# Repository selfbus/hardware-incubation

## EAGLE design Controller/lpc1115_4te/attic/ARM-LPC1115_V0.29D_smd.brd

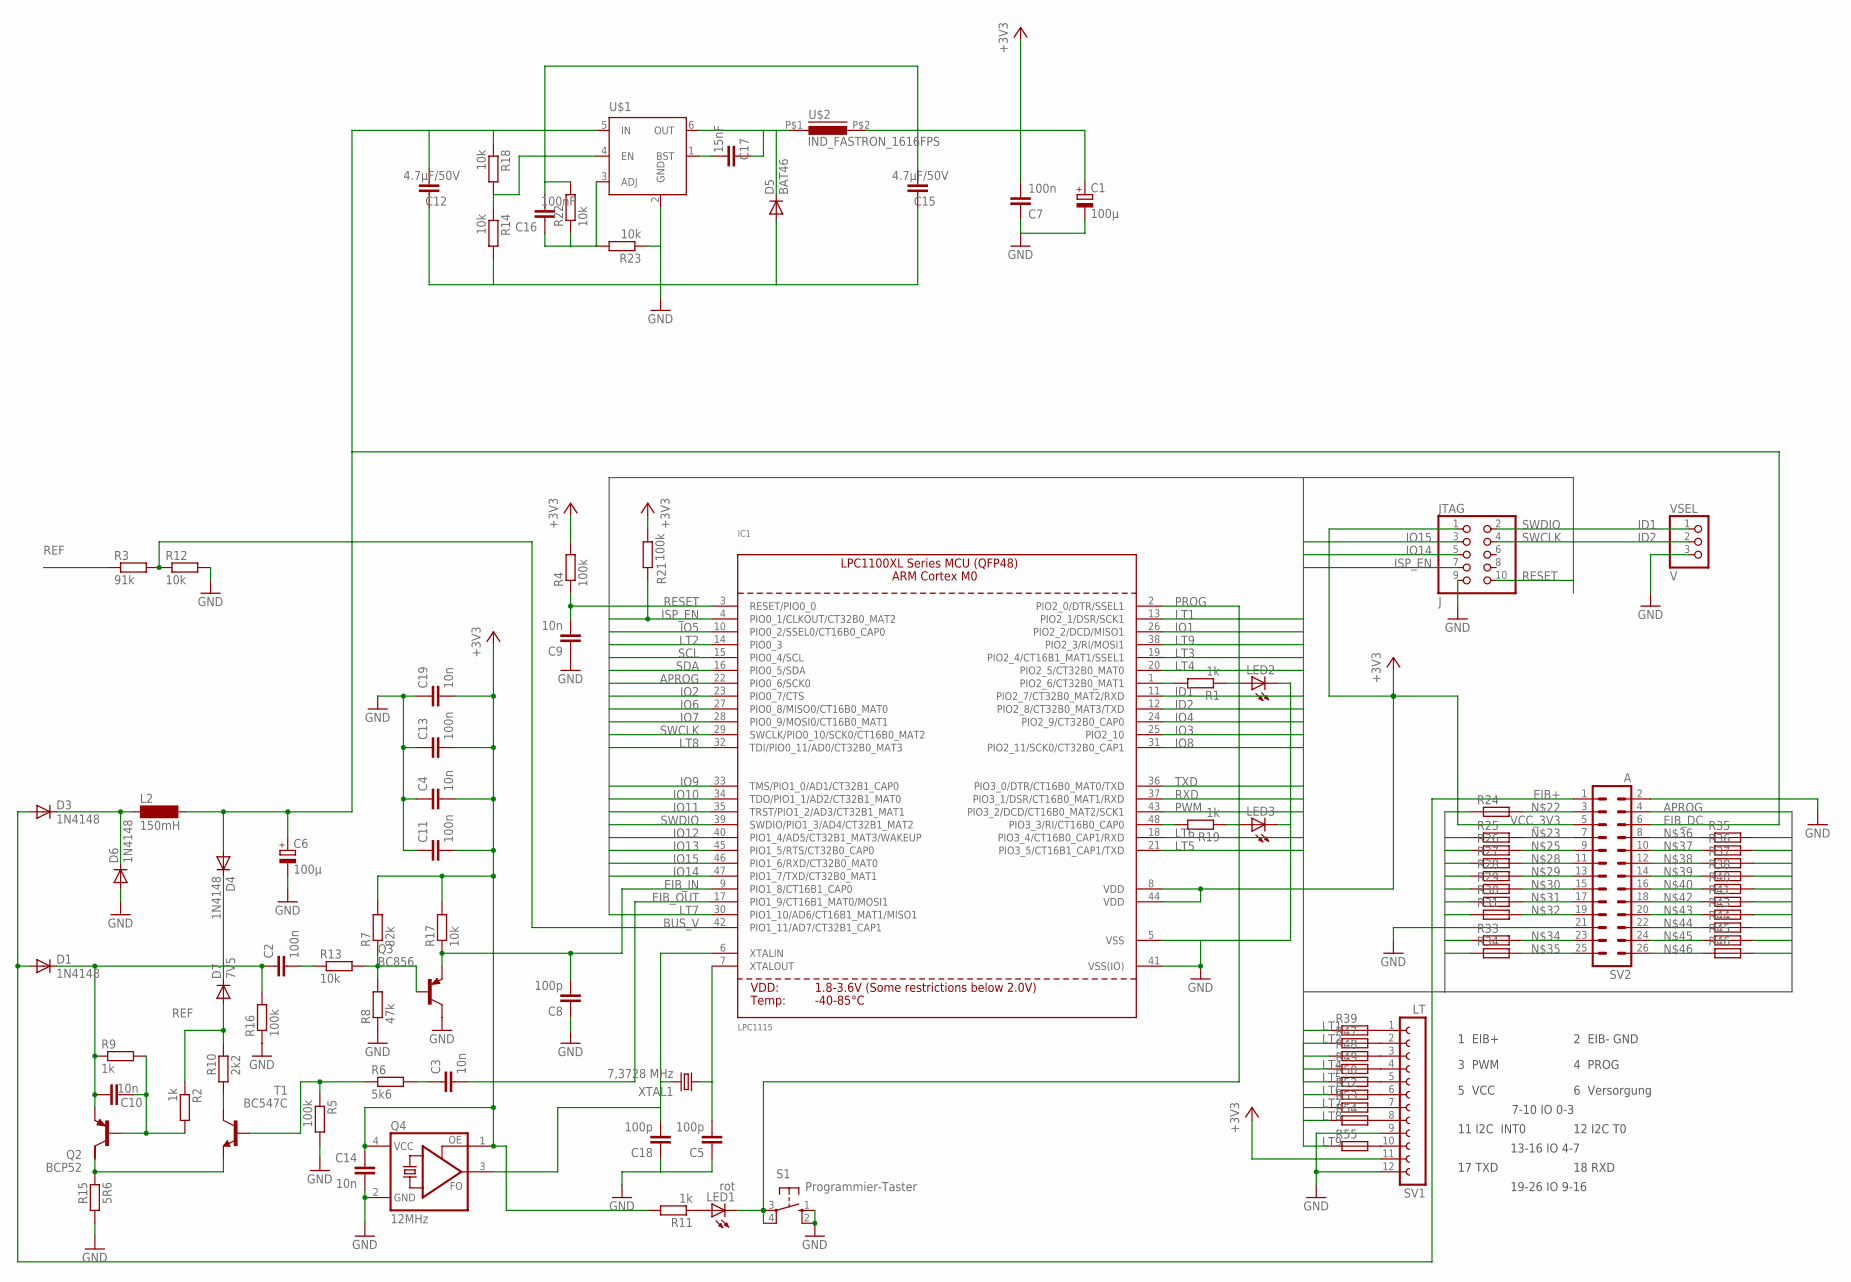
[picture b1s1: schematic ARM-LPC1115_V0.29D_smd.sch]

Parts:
C1, C6: 100µ; E5-8,5
C2: 100n; C1206K
C3, C9, C10: 10n; C1206K
C4, C14, C19: 10n; C1206
C5, C18: 100p; C0603
C7, C11, C13: 100n; C1206
C8: 100p; C1206K
C12, C15: 4.7µF/50V; C1206K
C16: 100nF; C1206
C17: 15nF; C1206
D1, D3, D4, D6: 1N4148; MINIMELF
D5: BAT46; DO214AC
D7: 7V5; MINIMELF
IC1: LPC1115; LQFP48
JTAG: J; 2X05M
L2: 150mH; SD12_1000
LED1: rot; LED3MM
LED2, LED3: LEDSMT1206; 1206
Q2: BCP52; SOT223
Q3: BC856; SOT23-BEC
Q4: 12MHz; ASF
R1, R2, R9, R11, R19: 1k; R1206
R3: 91k; R1206
R4, R5, R16, R21: 100k; R1206
R6: 5k6; R1206
R7: 82k; R1206
R8: 47k; R1206
R10: 2k2; R1206
R12, R13, R14, R17, R18, R22, R23: 10k; R1206
R15: 5R6; R1206
R24, R25, R26, R27, R28, R29, R30, R31, R33, R34, R35, R36, R37, R38, R39, R40, R41, R43, R44, R45, R46, R47, R48, R49, R50, R52, R53, R54, R55: R-EU_BRIDGER0603; R0603_BRIDGE
S1: Programmier-Taster; B3F-10XX
SV1: LT; FE12
SV2: A; ML26
T1: BC547C; SOT23
U$1: BD9G101GBD9G101G-SOT23-6; SOT23-6
U$2: IND_FASTRON_1616FPS; PIS2812
VSEL: V; 1X03_ROUND
XTAL1: 7,3728 MHz; HC49/S

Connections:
APROG: IC1.22 (PIO0_6/SCK0), SV2.4
BUS_V: IC1.42 (PIO1_11/AD7/CT32B1_CAP1), R3.2, R12.1
DRAIN: C2.1, C10.1, D1.C, Q2.3 (E), R9.1, R16.2
EIB+: D1.A, D3.A, SV2.1
EIB_DC: C6.+, C12.2, D4.A, L2.2, R18.1, SV2.6, U$1.5 (IN)
EIB_IN: C8.2, IC1.9 (PIO1_8/CT16B1_CAP0), Q3.E, R17.1
EIB_OUT: C3.2, IC1.17 (PIO1_9/CT16B1_MAT0/MOSI1)
GND: C1.-, C4.1, C5.1, C6.-, C7.1, C8.1, C9.1, C11.1, C12.1, C13.1, C14.2, C15.1, C18.1, C19.1, D5.A, D6.A, IC1.5 (VSS), IC1.41 (VSS(IO)), JTAG.9, LED2.C, LED3.C, Q3.C, Q4.2 (GND), R5.2, R8.1, R12.2, R14.2, R15.1, R16.1, R23.1, S1.1 (S), S1.2 (S1), SV1.9, SV1.12, SV2.2, SV2.21, U$1.2 (GND), VSEL.3
ID1: IC1.11 (PIO2_7/CT32B0_MAT2/RXD), VSEL.1
ID2: IC1.12 (PIO2_8/CT32B0_MAT3/TXD), VSEL.2
IO1: IC1.26 (PIO2_2/DCD/MISO1), R25.1
IO2: IC1.23 (PIO0_7/CTS), R35.2
IO3: IC1.25 (PIO2_10), R26.1
IO4: IC1.24 (PIO2_9/CT32B0_CAP0), R36.2
IO5: IC1.10 (PIO0_2/SSEL0/CT16B0_CAP0), R28.1
IO6: IC1.27 (PIO0_8/MISO0/CT16B0_MAT0), R38.2
IO7: IC1.28 (PIO0_9/MOSI0/CT16B0_MAT1), R29.1
IO8: IC1.31 (PIO2_11/SCK0/CT32B0_CAP1), R40.2
IO9: IC1.33 (TMS/PIO1_0/AD1/CT32B1_CAP0), R31.1
IO10: IC1.34 (TDO/PIO1_1/AD2/CT32B1_MAT0), R43.2
IO11: IC1.35 (TRST/PIO1_2/AD3/CT32B1_MAT1), R44.2
IO12: IC1.40 (PIO1_4/AD5/CT32B1_MAT3/WAKEUP), R33.1
IO13: IC1.45 (PIO1_5/RTS/CT32B0_CAP0), R45.2
IO14: IC1.47 (PIO1_7/TXD/CT32B0_MAT1), JTAG.5, R34.1
IO15: IC1.46 (PIO1_6/RXD/CT32B0_MAT0), JTAG.3, R46.2
ISP_EN: IC1.4 (PIO0_1/CLKOUT/CT32B0_MAT2), JTAG.7, R21.1
LT1: IC1.13 (PIO2_1/DSR/SCK1), R39.1
LT2: IC1.14 (PIO0_3), R47.1
LT3: IC1.19 (PIO2_4/CT16B1_MAT1/SSEL1), R48.1
LT4: IC1.20 (PIO2_5/CT32B0_MAT0), R49.1
LT5: IC1.21 (PIO3_5/CT16B1_CAP1/TXD), R50.1
LT6: IC1.18 (PIO3_4/CT16B0_CAP1/RXD), R52.1
LT7: IC1.30 (PIO1_10/AD6/CT16B1_MAT1/MISO1), R53.1
LT8: IC1.32 (TDI/PIO0_11/AD0/CT32B0_MAT3), R54.1
LT9: IC1.38 (PIO2_3/RI/MOSI1), R55.1
LX: C17.1, D5.C, U$1.6 (OUT), U$2.P$1 (1)
unnamed: C3.1, R6.2
unnamed: C2.2, R13.1
unnamed: C5.2, IC1.7 (XTALOUT), XTAL1.1
unnamed: IC1.1 (PIO2_6/CT32B0_MAT1), R1.2
unnamed: IC1.48 (PIO3_3/RI/CT16B0_CAP0), R19.2
unnamed: R10.1, T1.3 (C)
unnamed: Q2.2 (C), R15.2, T1.2 (E)
unnamed: D3.C, D6.C, L2.1
unnamed: D4.C, D7.C
unnamed: LED2.A, R1.1
unnamed: LED3.A, R19.1
unnamed: R5.1, R6.1, T1.1 (B)
unnamed: Q3.B, R7.1, R8.2, R13.2
unnamed: C10.2, Q2.1 (B), R2.2, R9.2
unnamed: C18.2, IC1.6 (XTALIN), Q4.3 (FO), XTAL1.2
unnamed: C17.2, U$1.1 (BST)
unnamed: R14.1, R18.2, U$1.4 (EN)
unnamed: R24.2, SV2.3
unnamed: R25.2, SV2.7
unnamed: C16.1, R22.1, R23.2, U$1.3 (ADJ)
unnamed: R26.2, SV2.9
unnamed: R27.2, SV2.11
unnamed: R28.2, SV2.13
unnamed: R29.2, SV2.15
unnamed: R30.2, SV2.17
unnamed: R31.2, SV2.19
unnamed: R33.2, SV2.23
unnamed: R34.2, SV2.25
unnamed: R35.1, SV2.8
unnamed: R36.1, SV2.10
unnamed: R37.1, SV2.12
unnamed: R38.1, SV2.14
unnamed: R40.1, SV2.16
unnamed: LED1.A, R11.1
unnamed: R41.1, SV2.18
unnamed: R43.1, SV2.20
unnamed: R44.1, SV2.22
unnamed: R45.1, SV2.24
unnamed: R46.1, SV2.26
unnamed: R39.2, SV1.1
unnamed: R47.2, SV1.2
unnamed: R48.2, SV1.3
unnamed: R49.2, SV1.4
unnamed: R50.2, SV1.5
unnamed: R52.2, SV1.6
unnamed: R53.2, SV1.7
unnamed: R54.2, SV1.8
unnamed: R55.2, SV1.10
PROG: IC1.2 (PIO2_0/DTR/SSEL1), LED1.K (C), S1.3, S1.4 (P1)
PWM: IC1.43 (PIO3_2/DCD/CT16B0_MAT2/SCK1), R24.1
REF: D7.A, R2.1, R3.1, R10.2
RESET: C9.2, IC1.3 (RESET/PIO0_0), JTAG.10, R4.1
RXD: IC1.37 (PIO3_1/DSR/CT16B0_MAT1/RXD), R41.2
SCL: IC1.15 (PIO0_4/SCL), R37.2
SDA: IC1.16 (PIO0_5/SDA), R27.1
SWCLK: IC1.29 (SWCLK/PIO0_10/SCK0/CT16B0_MAT2), JTAG.4
SWDIO: IC1.39 (SWDIO/PIO1_3/AD4/CT32B1_MAT2), JTAG.2
TXD: IC1.36 (PIO3_0/DTR/CT16B0_MAT0/TXD), R30.1
VCC_3V3: C1.+, C4.2, C7.2, C11.2, C13.2, C14.1, C15.2, C16.2, C19.2, IC1.8 (VDD), IC1.44 (VDD), JTAG.1, Q4.1 (OE), Q4.4 (VCC), R4.2, R7.2, R11.2, R17.2, R21.2, R22.2, SV1.11, SV2.5, U$2.P$2 (2)

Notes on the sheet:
1 EIB+
2 EIB- GND
3 PWM
4 PROG
5 VCC
6 Versorgung
7-10 IO 0-3
11 I2C INT0
12 I2C T0
13-16 IO 4-7
17 TXD
18 RXD
19-26 IO 9-16

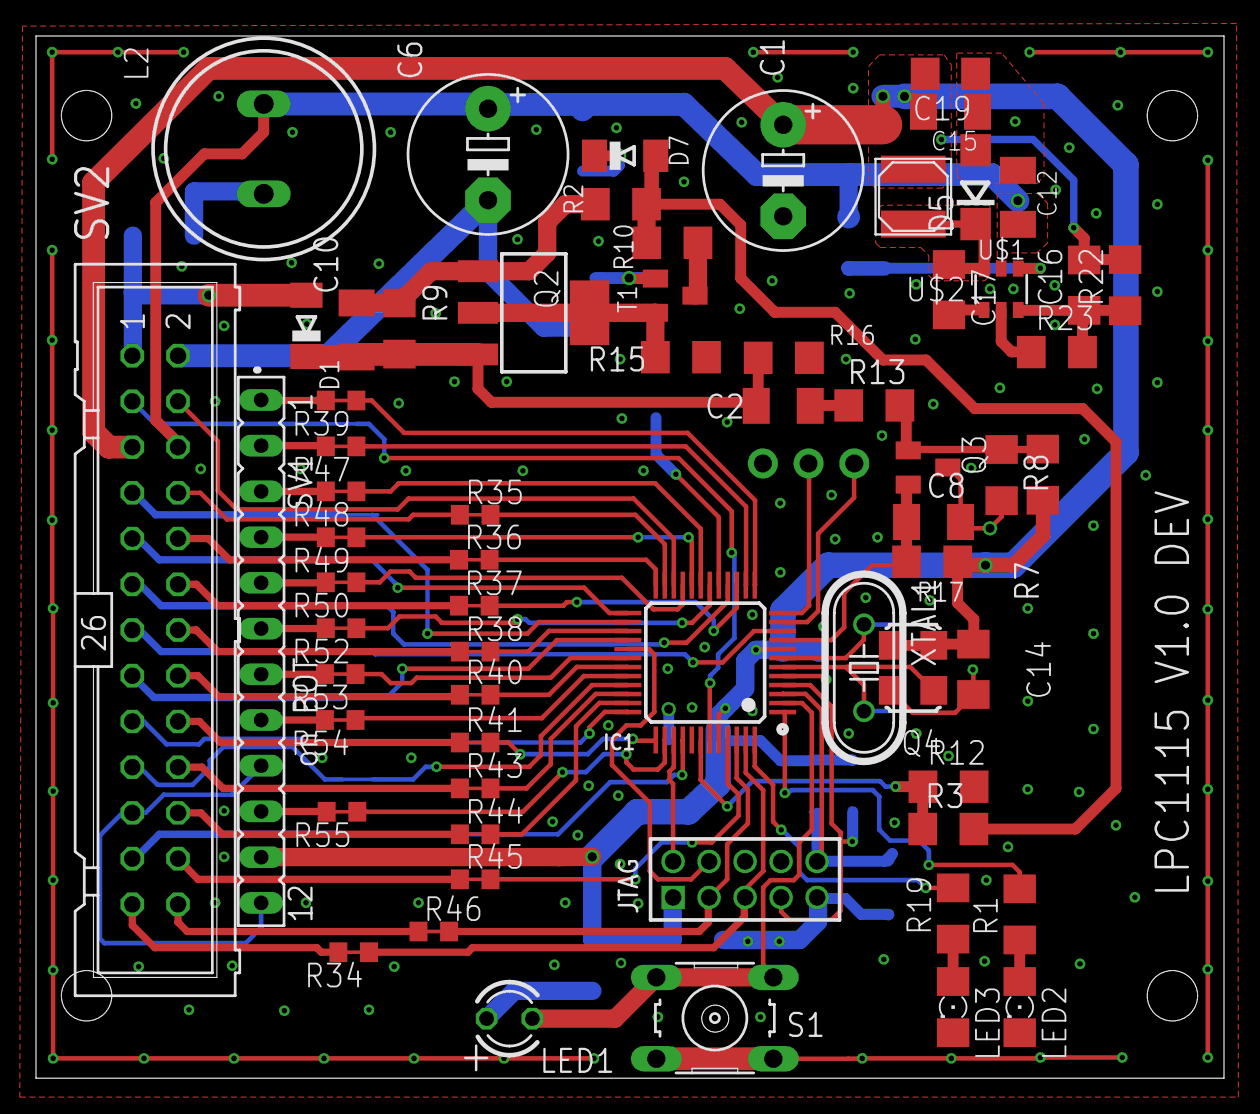
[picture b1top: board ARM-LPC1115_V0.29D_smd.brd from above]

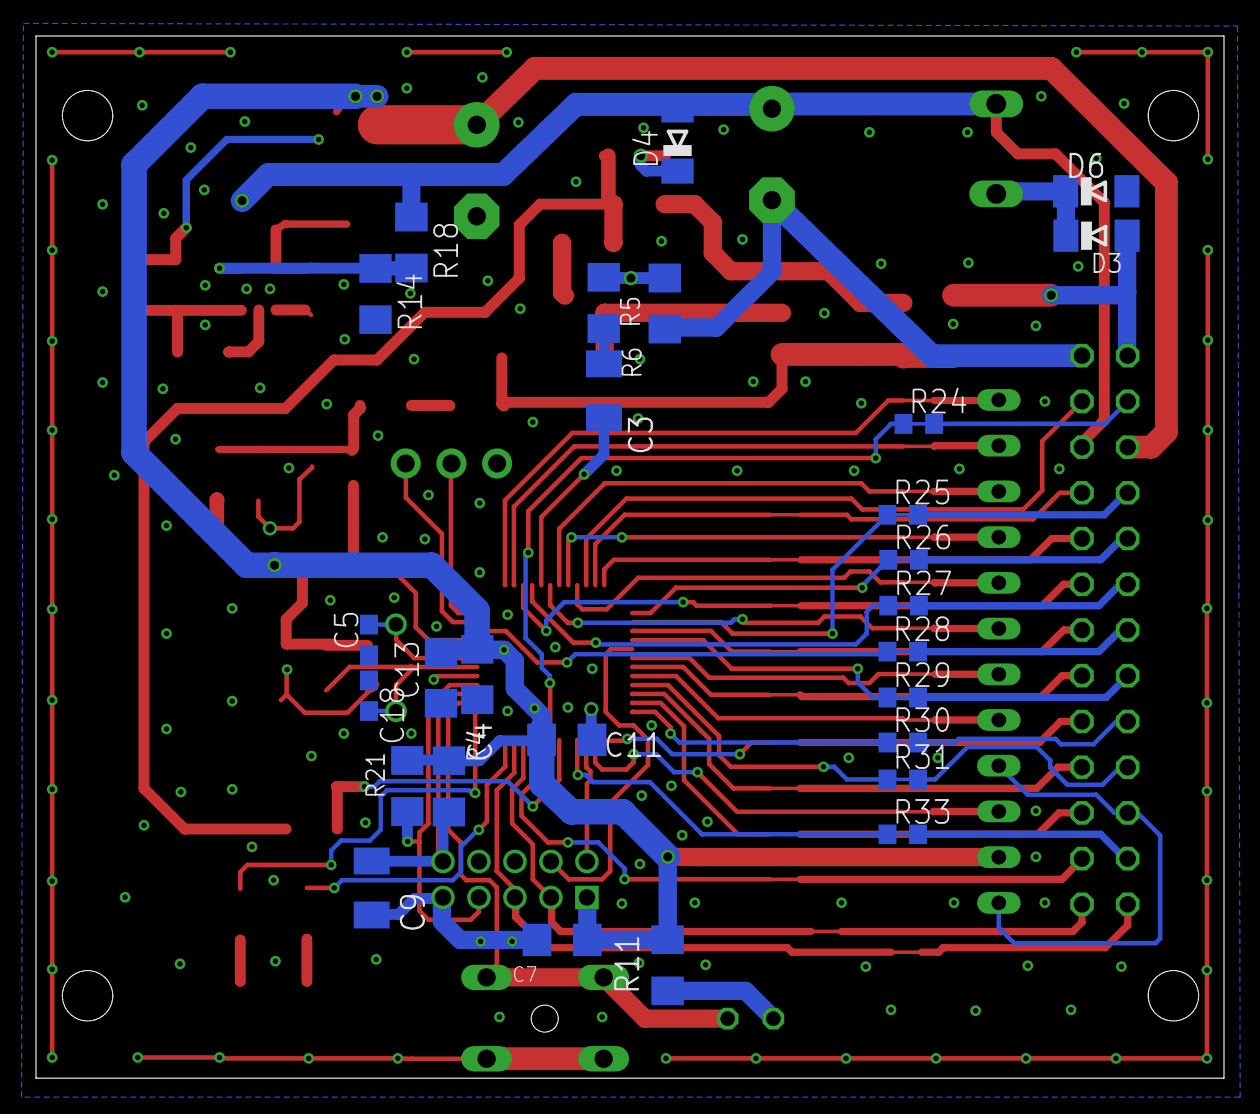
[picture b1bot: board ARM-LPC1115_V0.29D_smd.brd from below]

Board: 2 copper layers, 66.0 x 57.9 mm, 93 parts (27 on the bottom side), 95 nets.

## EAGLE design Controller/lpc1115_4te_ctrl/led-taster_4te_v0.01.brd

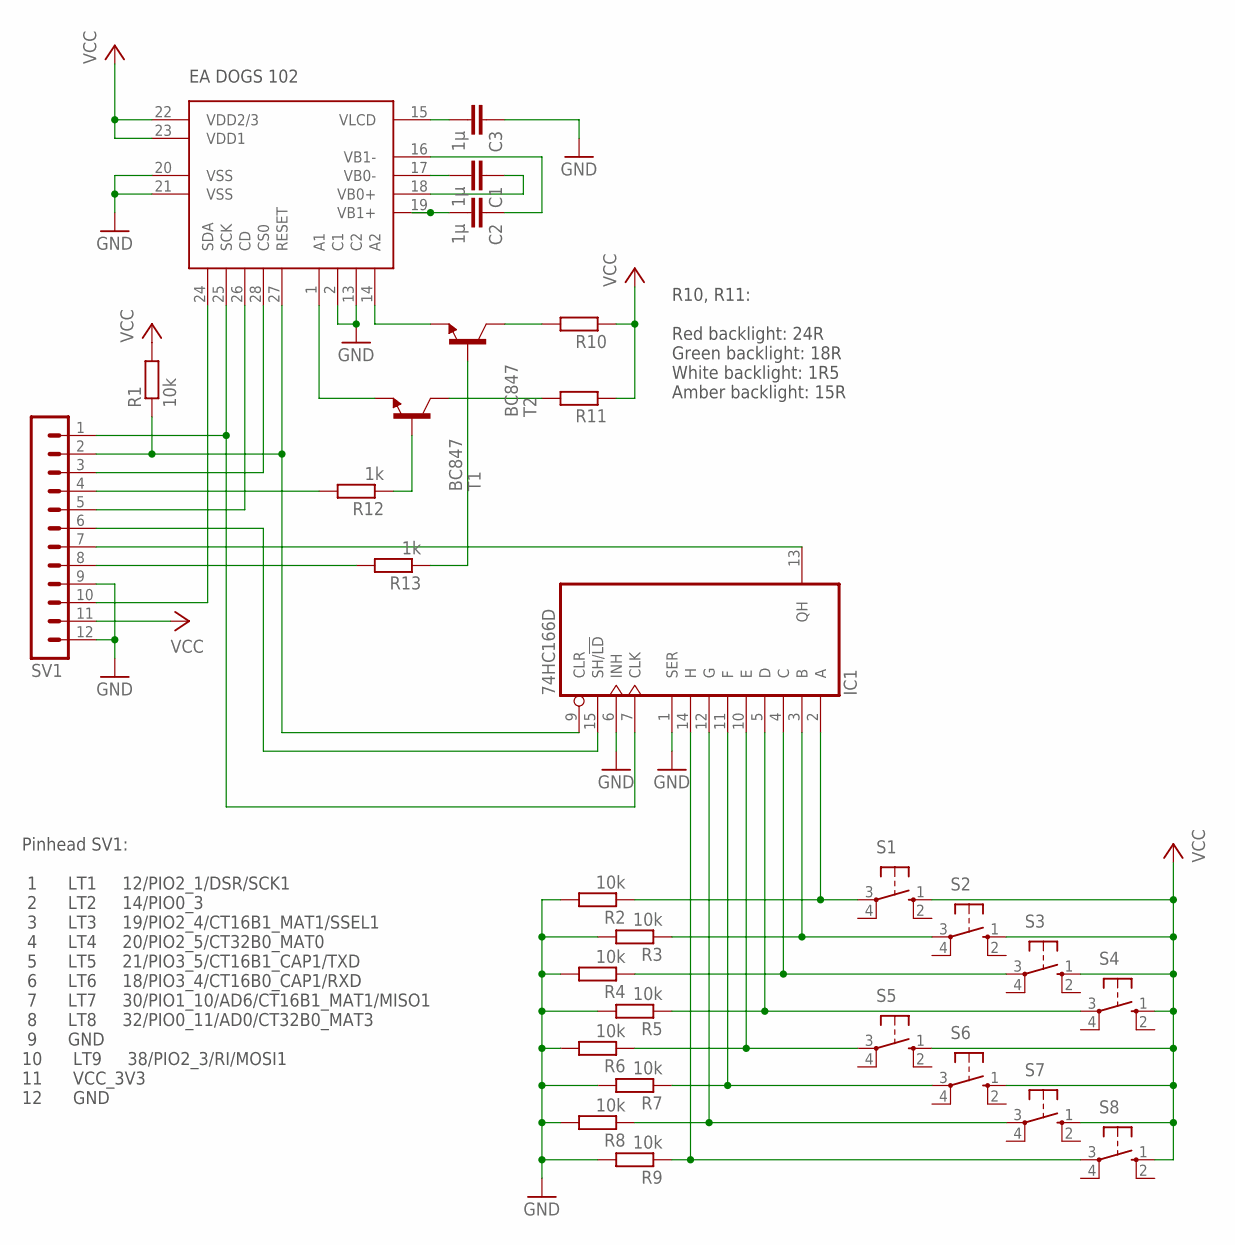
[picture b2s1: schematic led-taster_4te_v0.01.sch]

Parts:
C1, C2, C3: 1µ; C1210
EA_DOGS102: DOGS102
IC1: 74HC166D; SO16
R1, R2, R3, R4, R5, R6, R7, R8, R9: 10k; R1206
R10, R11: R-EU_R1206; R1206
R12, R13: 1k; R1206
S1, S2, S3, S4, S5, S6, S7, S8: 10-XX; B3F-10XX
SV1: MA12-1
T1, T2: BC847; SOT23

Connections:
+3V3: EA_DOGS102.22 (VDD2/3), EA_DOGS102.23 (VDD1), IC1.16 (VCC), R1.2, R10.1, R11.1, S1.1 (S), S2.1 (S), S3.1 (S), S4.1 (S), S5.1 (S), S6.1 (S), S7.1 (S), S8.1 (S), SV1.11
GND: C3.1, EA_DOGS102.2 (C1), EA_DOGS102.13 (C2), EA_DOGS102.20 (VSS), EA_DOGS102.21 (VSS), IC1.1 (SER), IC1.6 (INH), IC1.8 (GND), R2.2, R3.2, R4.2, R5.2, R6.2, R7.2, R8.2, R9.2, SV1.9, SV1.12
MISO: IC1.13 (QH), SV1.7
MOSI: EA_DOGS102.24 (SDA), SV1.10
unnamed: IC1.2 (A), R2.1, S1.3
unnamed: C2.2, EA_DOGS102.19 (VB1+)
unnamed: C2.1, EA_DOGS102.16 (VB1-)
unnamed: C1.2, EA_DOGS102.17 (VB0-)
unnamed: C1.1, EA_DOGS102.18 (VB0+)
unnamed: C3.2, EA_DOGS102.15 (VLCD)
unnamed: IC1.3 (B), R3.1, S2.3
unnamed: IC1.4 (C), R4.1, S3.3
unnamed: IC1.5 (D), R5.1, S4.3
unnamed: IC1.10 (E), R6.1, S5.3
unnamed: IC1.14 (H), R9.1, S8.3
unnamed: IC1.12 (G), R8.1, S7.3
unnamed: IC1.11 (F), R7.1, S6.3
unnamed: EA_DOGS102.28 (CS0), SV1.3
unnamed: EA_DOGS102.1 (A1), T1.2 (E)
unnamed: EA_DOGS102.14 (A2), T2.2 (E)
unnamed: R10.2, T2.3 (C)
unnamed: R11.2, T1.3 (C)
unnamed: R13.1, T2.1 (B)
unnamed: R12.1, T1.1 (B)
unnamed: R12.2, SV1.4
unnamed: R13.2, SV1.8
unnamed: IC1.15 (SH/!LD), SV1.6
unnamed: EA_DOGS102.26 (CD), SV1.5
RESET: EA_DOGS102.27 (RESET), IC1.9 (CLR), R1.1, SV1.2
SCK: EA_DOGS102.25 (SCK), IC1.7 (CLK), SV1.1

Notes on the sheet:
Pinhead SV1: 1 LT1 12/PIO2_1/DSR/SCK1 2 LT2 14/PIO0_3 3 LT3 19/PIO2_4/CT16B1_MAT1/SSEL1 4 LT4 20/PIO2_5/CT32B0_MAT0 5 LT5 21/PIO3_5/CT16B1_CAP1/TXD 6 LT6 18/PIO3_4/CT16B0_CAP1/RXD 7 LT7 30/PIO1_10/AD6/CT16B1_MAT1/MISO1 8 LT8 32/PIO0_11/AD0/CT32B0_MAT3 9 GND 10 LT9 38/PIO2_3/RI/MOSI1 11 VCC_3V3 12 G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
R10, R11: Red backlight: 24R Green backlight: 18R White backlight: 1R5 Amber backlight: 15R
EA DOGS 102

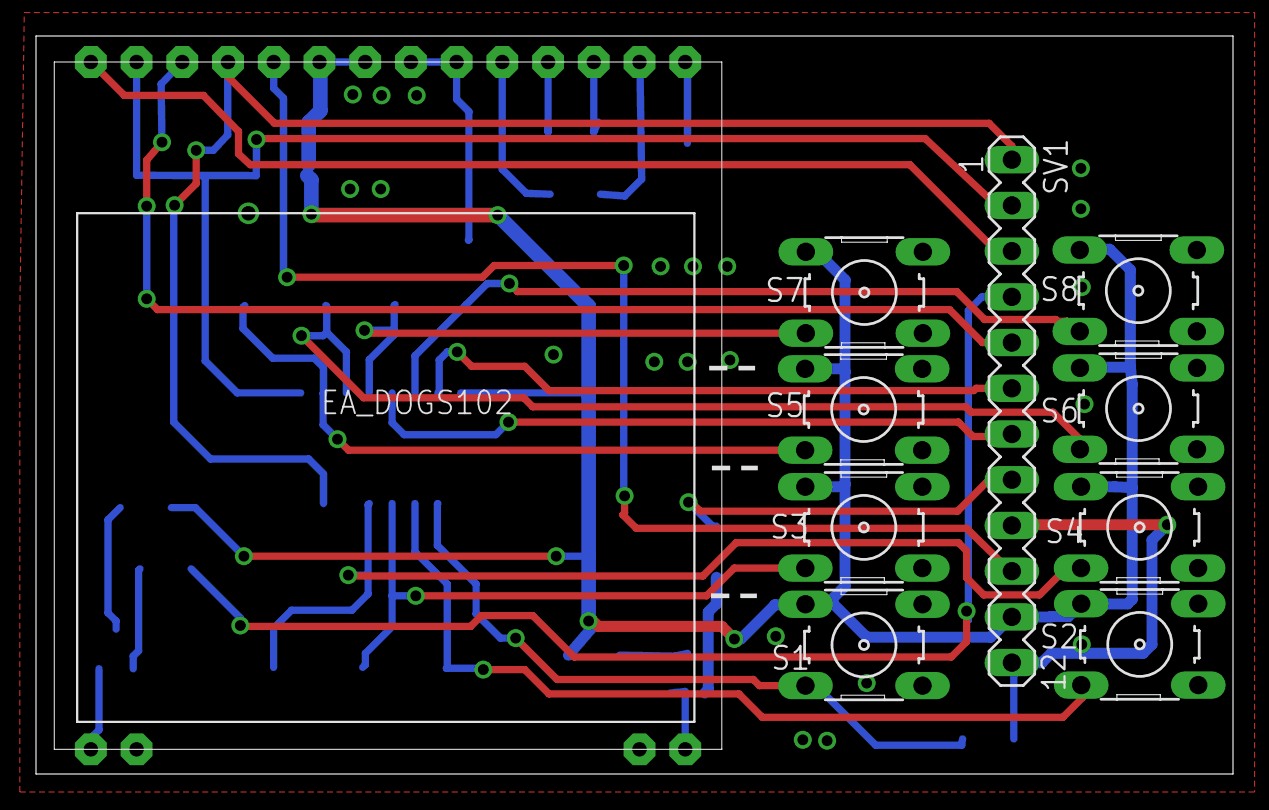
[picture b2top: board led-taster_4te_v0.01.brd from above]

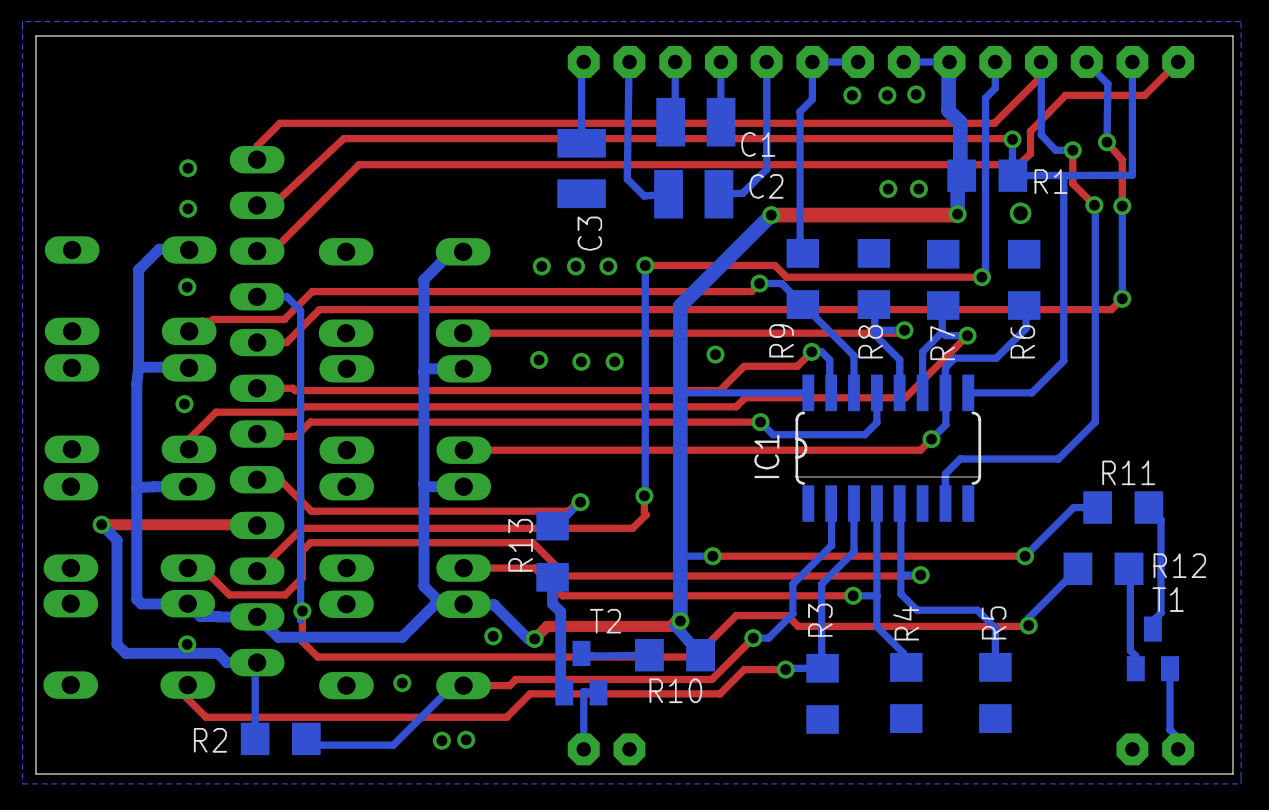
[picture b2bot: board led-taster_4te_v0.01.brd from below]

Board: 2 copper layers, 66.5 x 41.0 mm, 29 parts (19 on the bottom side), 30 nets.

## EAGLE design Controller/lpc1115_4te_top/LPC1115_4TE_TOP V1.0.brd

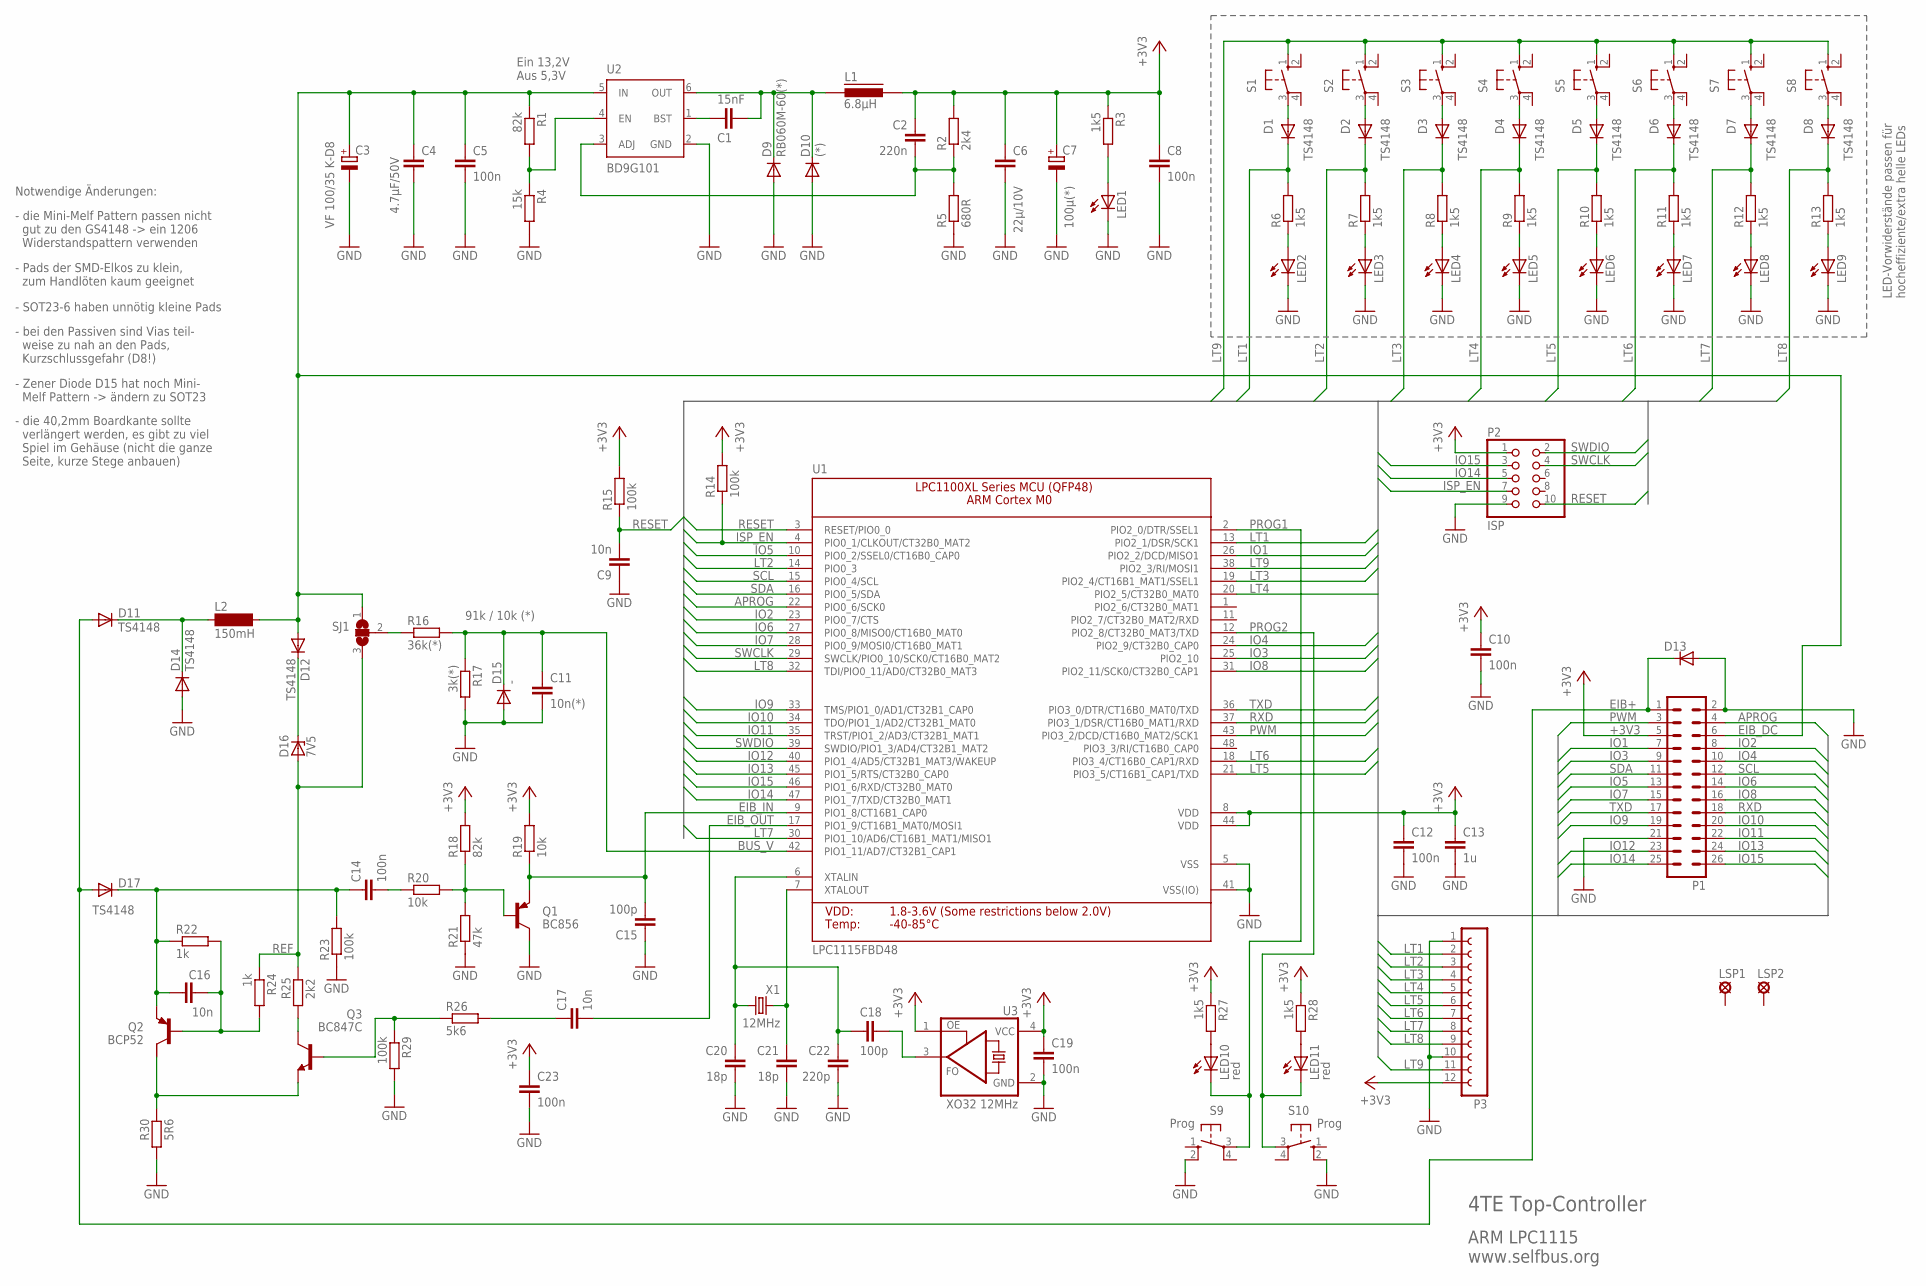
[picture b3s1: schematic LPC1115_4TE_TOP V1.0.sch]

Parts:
C1: 15nF; R0805M
C2: 220n; R0805M
C3: VF 100/35 K-D8; UD-6,3X7,7_NICHICON
C4: 4.7µF/50V; R1206M
C5, C8, C10, C12, C14, C19, C23: 100n; R0805M
C6: 22µ/10V; C1210K
C7: 100µ(*); UD-6,3X7,7_NICHICON
C9, C16, C17: 10n; R0805M
C11: 10n(*); R0805M
C13: 1u; R0805M
C15, C18: 100p; R0805M
C20, C21: 18p; R0805M
C22: 220p; R0805M
D1, D2, D3, D4, D5, D6, D7, D8, D11, D12, D14, D17: TS4148; MINIMELF
D9: RB060M-60(*); SOD123
D10: (*); SMB
D13: D-SMB; SMB
D15: -; MINIMELF
D16: 7V5; SOT23
L1: 6.8µH; 1616FPS
L2: 150mH; BS11_LIEGEND
LED1, LED2, LED3, LED4, LED5, LED6, LED7, LED8, LED9: LEDSMT1206; 1206
LED10, LED11: red; 1206
LSP1, LSP2: SE13_SM
P1: ML26
P2: ISP; 2X05M
P3: FE12-1; FE12
Q1: BC856; SOT23-BEC
Q2: BCP52; SOT223
Q3: BC847C; SOT23
R1, R18: 82k; R0805M
R2: 2k4; R0805M
R3, R6, R7, R8, R9, R10, R11, R12, R13, R27, R28: 1k5; R0805M
R4: 15k; R0805M
R5: 680R; R0805M
R14, R15, R23, R29: 100k; R0805M
R16: 36k(*); R0805M
R17: 3k(*); R0805M
R19, R20: 10k; R0805M
R21: 47k; R0805M
R22, R24: 1k; R0805M
R25: 2k2; R0805M
R26: 5k6; R0805M
R30: 5R6; R1206M
S1, S2, S3, S4, S5, S6, S7, S8: 10-XXSMD; B3F-10XX_SMD
S9, S10: Prog; B3F-10XX_SMD
SJ1: SJ2W; SJ_2
U1: LPC1115FBD48; LQFP48
U2: BD9G101; SOT23-6
U3: XO32 12MHz; ASF
X1: 12MHz; ASF

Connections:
+3V3: C2.1, C6.1, C7.+, C8.1, C10.1, C12.1, C13.1, C19.1, C23.1, L1.P$2 (2), P1.5, P2.1, P3.12, R2.2, R3.1, R14.2, R15.2, R18.2, R19.2, R27.1, R28.1, U1.8 (VDD), U1.44 (VDD), U3.1 (OE), U3.4 (VCC)
APROG: P1.4, U1.22 (PIO0_6/SCK0)
BUS_V: C11.1, D15.C, R16.2, R17.1, U1.42 (PIO1_11/AD7/CT32B1_CAP1)
DRAIN: C14.1, C16.1, D17.C, Q2.3 (E), R22.1, R23.2
EIB+: D11.A, D13.1 (C), D17.A, P1.1
EIB_DC: C3.+, C4.1, C5.1, D12.A, L2.2, P1.6, R1.1, SJ1.1, U2.5 (IN)
EIB_IN: C15.2, Q1.E, R19.1, U1.9 (PIO1_8/CT16B1_CAP0)
EIB_OUT: C17.2, U1.17 (PIO1_9/CT16B1_MAT0/MOSI1)
GND: C3.-, C4.2, C5.2, C6.2, C7.-, C8.2, C9.1, C10.2, C11.2, C12.2, C13.2, C15.1, C19.2, C20.2, C21.2, C22.2, C23.2, D9.A, D10.A, D13.2 (A), D14.A, D15.A, LED1.C, LED2.C, LED3.C, LED4.C, LED5.C, LED6.C, LED7.C, LED8.C, LED9.C, P1.2, P1.21, P2.9, P3.1, P3.10, Q1.C, R4.2, R5.1, R17.2, R21.1, R23.1, R29.2, R30.1, S9.2 (S1), S10.2 (S1), U1.5 (VSS), U1.41 (VSS(IO)), U2.2 (GND), U3.2 (GND)
IO1: P1.7, U1.26 (PIO2_2/DCD/MISO1)
IO2: P1.8, U1.23 (PIO0_7/CTS)
IO3: P1.9, U1.25 (PIO2_10)
IO4: P1.10, U1.24 (PIO2_9/CT32B0_CAP0)
IO5: P1.13, U1.10 (PIO0_2/SSEL0/CT16B0_CAP0)
IO6: P1.14, U1.27 (PIO0_8/MISO0/CT16B0_MAT0)
IO7: P1.15, U1.28 (PIO0_9/MOSI0/CT16B0_MAT1)
IO8: P1.16, U1.31 (PIO2_11/SCK0/CT32B0_CAP1)
IO9: P1.19, U1.33 (TMS/PIO1_0/AD1/CT32B1_CAP0)
IO10: P1.20, U1.34 (TDO/PIO1_1/AD2/CT32B1_MAT0)
IO11: P1.22, U1.35 (TRST/PIO1_2/AD3/CT32B1_MAT1)
IO12: P1.23, U1.40 (PIO1_4/AD5/CT32B1_MAT3/WAKEUP)
IO13: P1.24, U1.45 (PIO1_5/RTS/CT32B0_CAP0)
IO14: P1.25, P2.5, U1.47 (PIO1_7/TXD/CT32B0_MAT1)
IO15: P1.26, P2.3, U1.46 (PIO1_6/RXD/CT32B0_MAT0)
ISP_EN: P2.7, R14.1, U1.4 (PIO0_1/CLKOUT/CT32B0_MAT2)
LT1: D1.C, P3.2, R6.2, U1.13 (PIO2_1/DSR/SCK1)
LT2: D2.C, P3.3, R7.2, U1.14 (PIO0_3)
LT3: D3.C, P3.4, R8.2, U1.19 (PIO2_4/CT16B1_MAT1/SSEL1)
LT4: D4.C, P3.5, R9.2, U1.20 (PIO2_5/CT32B0_MAT0)
LT5: D5.C, P3.6, R10.2, U1.21 (PIO3_5/CT16B1_CAP1/TXD)
LT6: D6.C, P3.7, R11.2, U1.18 (PIO3_4/CT16B0_CAP1/RXD)
LT7: D7.C, P3.8, R12.2, U1.30 (PIO1_10/AD6/CT16B1_MAT1/MISO1)
LT8: D8.C, P3.9, R13.2, U1.32 (TDI/PIO0_11/AD0/CT32B0_MAT3)
LT9: P3.11, S1.1 (S), S2.1 (S), S3.1 (S), S4.1 (S), S5.1 (S), S6.1 (S), S7.1 (S), S8.1 (S), U1.38 (PIO2_3/RI/MOSI1)
LX: C1.1, D9.C, D10.C, L1.P$1 (1), U2.6 (OUT)
unnamed: C17.1, R26.2
unnamed: C14.2, R20.1
unnamed: C21.1, U1.7 (XTALOUT), X1.1
unnamed: LED11.A, R28.2
unnamed: R16.1, SJ1.2
unnamed: Q3.3 (C), R25.1
unnamed: Q2.2 (C), Q3.2 (E), R30.2
unnamed: D11.C, D14.C, L2.1
unnamed: D12.C, D16.3 (C)
unnamed: Q3.1 (B), R26.1, R29.1
unnamed: LED1.A, R3.2
unnamed: Q1.B, R18.1, R20.2, R21.2
unnamed: C16.2, Q2.1 (B), R22.2, R24.2
unnamed: C18.1, U3.3 (FO)
unnamed: D8.A, S8.3
unnamed: C1.2, U2.1 (BST)
unnamed: R1.2, R4.1, U2.4 (EN)
unnamed: C18.2, C20.1, C22.1, U1.6 (XTALIN), X1.3 (2)
unnamed: D7.A, S7.3
unnamed: C2.2, R2.1, R5.2, U2.3 (ADJ)
unnamed: LED2.A, R6.1
unnamed: D6.A, S6.3
unnamed: D5.A, S5.3
unnamed: D4.A, S4.3
unnamed: D3.A, S3.3
unnamed: D2.A, S2.3
unnamed: LED3.A, R7.1
unnamed: D1.A, S1.3
unnamed: LED10.A, R27.2
unnamed: LED4.A, R8.1
unnamed: LED5.A, R9.1
unnamed: LED6.A, R10.1
unnamed: LED7.A, R11.1
unnamed: LED8.A, R12.1
unnamed: LED9.A, R13.1
PROG1: LED10.C, S9.3, U1.2 (PIO2_0/DTR/SSEL1)
PROG2: LED11.C, S10.3, U1.12 (PIO2_8/CT32B0_MAT3/TXD)
PWM: P1.3, U1.43 (PIO3_2/DCD/CT16B0_MAT2/SCK1)
REF: D16.1 (A), R24.1, R25.2, SJ1.3
RESET: C9.2, P2.10, R15.1, U1.3 (RESET/PIO0_0)
RXD: P1.18, U1.37 (PIO3_1/DSR/CT16B0_MAT1/RXD)
SCL: P1.12, U1.15 (PIO0_4/SCL)
SDA: P1.11, U1.16 (PIO0_5/SDA)
SWCLK: P2.4, U1.29 (SWCLK/PIO0_10/SCK0/CT16B0_MAT2)
SWDIO: P2.2, U1.39 (SWDIO/PIO1_3/AD4/CT32B1_MAT2)
TXD: P1.17, U1.36 (PIO3_0/DTR/CT16B0_MAT0/TXD)

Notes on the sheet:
4TE Top-Controller
ARM LPC1115 www.selfbus.org
Ein 13,2V Aus 5,3V
- die Mini-Melf Pattern passen nicht gut zu den GS4148 -> ein 1206 Widerstandspattern verwenden
Notwendige Änderungen:
91k / 10k (*)
- Pads der SMD-Elkos zu klein, zum Handlöten kaum geeignet
- SOT23-6 haben unnötig kleine Pads
- bei den Passiven sind Vias teil- weise zu nah an den Pads, Kurzschlussgefahr (D8!)
LED-Vorwiderstände passen für hocheffiziente/extra helle LEDs
- Zener Diode D15 hat noch Mini- Melf Pattern -> ändern zu SOT23
- die 40,2mm Boardkante sollte verlängert werden, es gibt zu viel Spiel im Gehäuse (nicht die ganze Seite, kurze Stege anbauen)

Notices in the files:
parts and their libraries:
microbuilder: This work is placed in the public domain, and may be freely used for commercial and non-commercial work with the following conditions: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
